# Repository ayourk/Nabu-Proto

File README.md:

# Nabu-Proto
My take on Swiss cheese for the Nabu PC.<br >
A Nabu PC Prototyping Expansion Card.

## Description
My interpretation of what a Nabu PC Prototyping Expansion Card should be. Designed using KiCAD 6.0.x

### PCB Layout

### See Also
[Nabu SD Card Expansion & More!](https://github.com/ayourk/Nabu-SD/tree/main/kicad)<br />
[Nabu PC PCB Schematics](https://github.com/ayourk/Nabu-PC) (work in progress)

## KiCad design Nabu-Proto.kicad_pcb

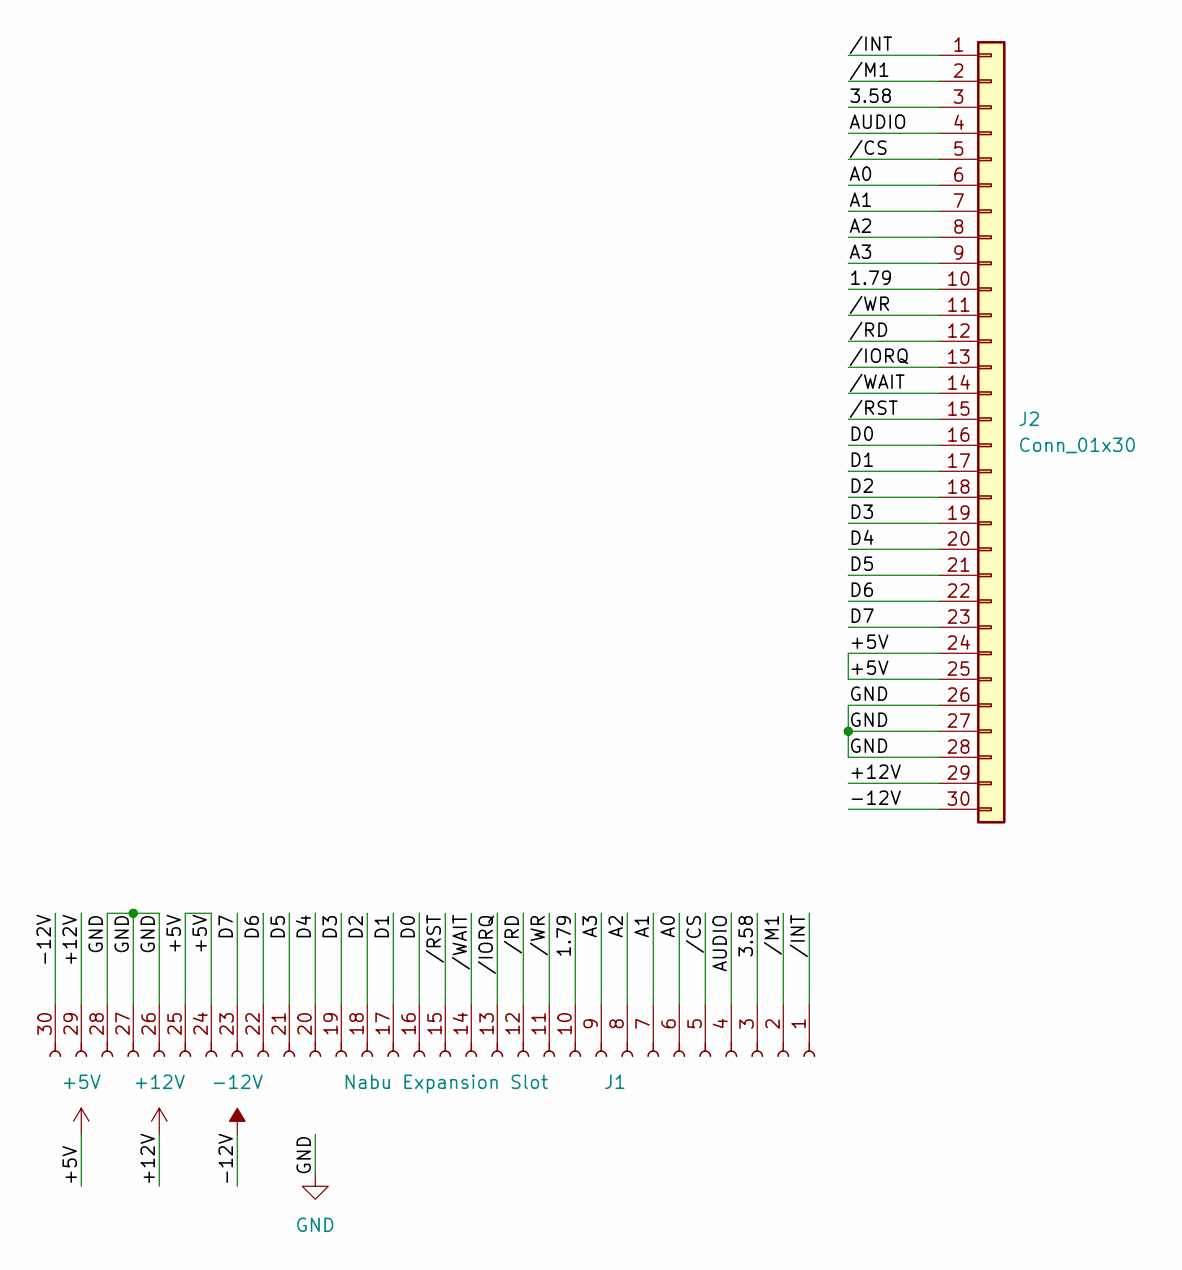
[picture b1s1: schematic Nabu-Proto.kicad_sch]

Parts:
J1: Nabu Expansion Slot; PinSocket_1x30_P2.54mm_Vertical; MPN SSW-130-22-F-S-RA; LCSC C6302891
J2: Conn_01x30; PinHeader_1x30_P2.54mm_Vertical; MPN TSW-1-30-09-T-S-RA; Digi-Key_PN 612-TSW-130-09-T-S-RA-ND

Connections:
+5V: J1.24, J1.25, J2.24, J2.25
+12V: J1.29, J2.29
-12V: J1.30, J2.30
/1.79: J1.10, J2.10
/3.58: J1.3, J2.3
/A0: J1.6, J2.6
/A1: J1.7, J2.7
/A2: J1.8, J2.8
/A3: J1.9, J2.9
/AUDIO: J1.4, J2.4
/D0: J1.16, J2.16
/D1: J1.17, J2.17
/D2: J1.18, J2.18
/D3: J1.19, J2.19
/D4: J1.20, J2.20
/D5: J1.21, J2.21
/D6: J1.22, J2.22
/D7: J1.23, J2.23
//CS: J1.5, J2.5
//INT: J1.1, J2.1
//IORQ: J1.13, J2.13
//M1: J1.2, J2.2
//RD: J1.12, J2.12
//RST: J1.15, J2.15
//WAIT: J1.14, J2.14
//WR: J1.11, J2.11
GND: J1.26, J1.27, J1.28, J2.26, J2.27, J2.28

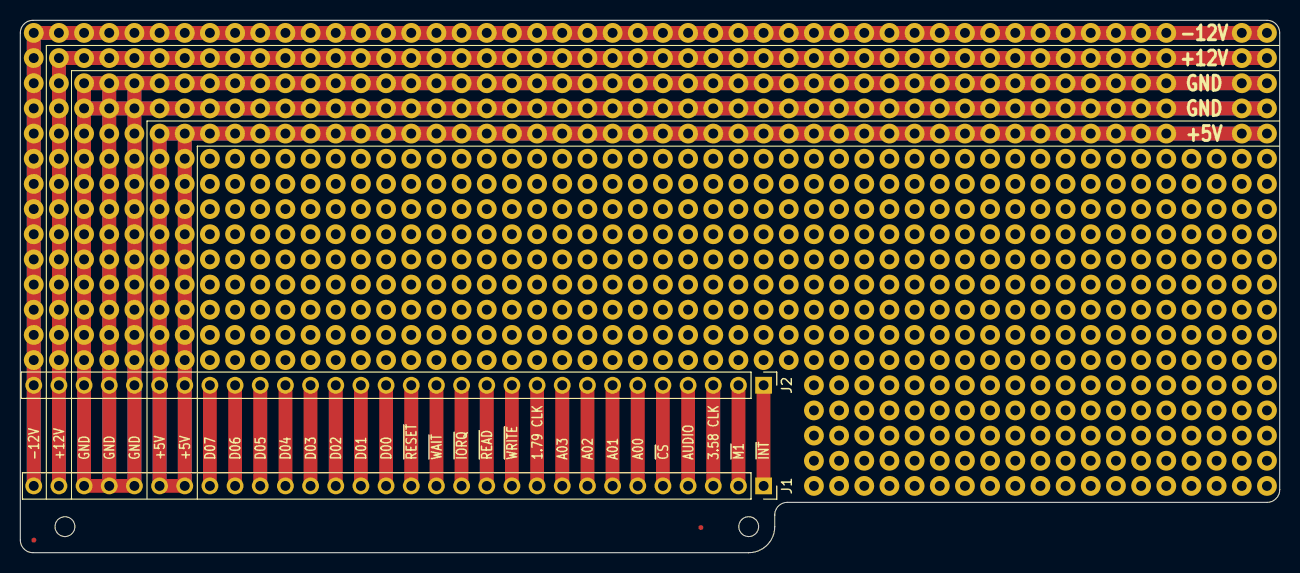
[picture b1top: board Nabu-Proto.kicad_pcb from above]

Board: 2 copper layers, 127.1 x 53.7 mm, 6 parts (0 on the bottom side), 27 nets.

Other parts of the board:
REF1, REF2: Fiducial_0.5mm_Mask1mm
REF3, REF4: MountingHole_2mm

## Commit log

2024-04-15 Primary commit for Nabu PC Proto board.
2024-04-15 Update README.md
    Initial Readme
